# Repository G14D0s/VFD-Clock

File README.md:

# VFD-Clock
Mein Projekt für LF06: Das Wiedererwecken einer Fluoreszenz-Anzeige. 

# Ressourcen
Die Dokumentation / Ausarbeitung findet sich hier:
* [VFD - Ausarbeitung](Documentation/VFD-Ausarbeitung.md)
* [Videos](https://drive.google.com/drive/folders/1unJfzBfumFYsPnYGjSA5P8ESAhW6MluK?usp=sharing)
* [neuester Release mit PDF](https://github.com/G14D0s/VFD-Clock/releases/tag/Release)

***
# Diagramme
Mit [Obsidian](https://obsidian.md/) habe ich folgende Canvas-Dateien erstellt:
* [elektrischer Aufbau/Verbindungen](Documentation/VFD-Aufbau.png)
* [Konzept Programmierung](Documentation/VFD-Bildschirm_Programmierung.png)
* [Ablauf Multiplexing](Documentation/Ablauf_Multiplexing_VFD.png)

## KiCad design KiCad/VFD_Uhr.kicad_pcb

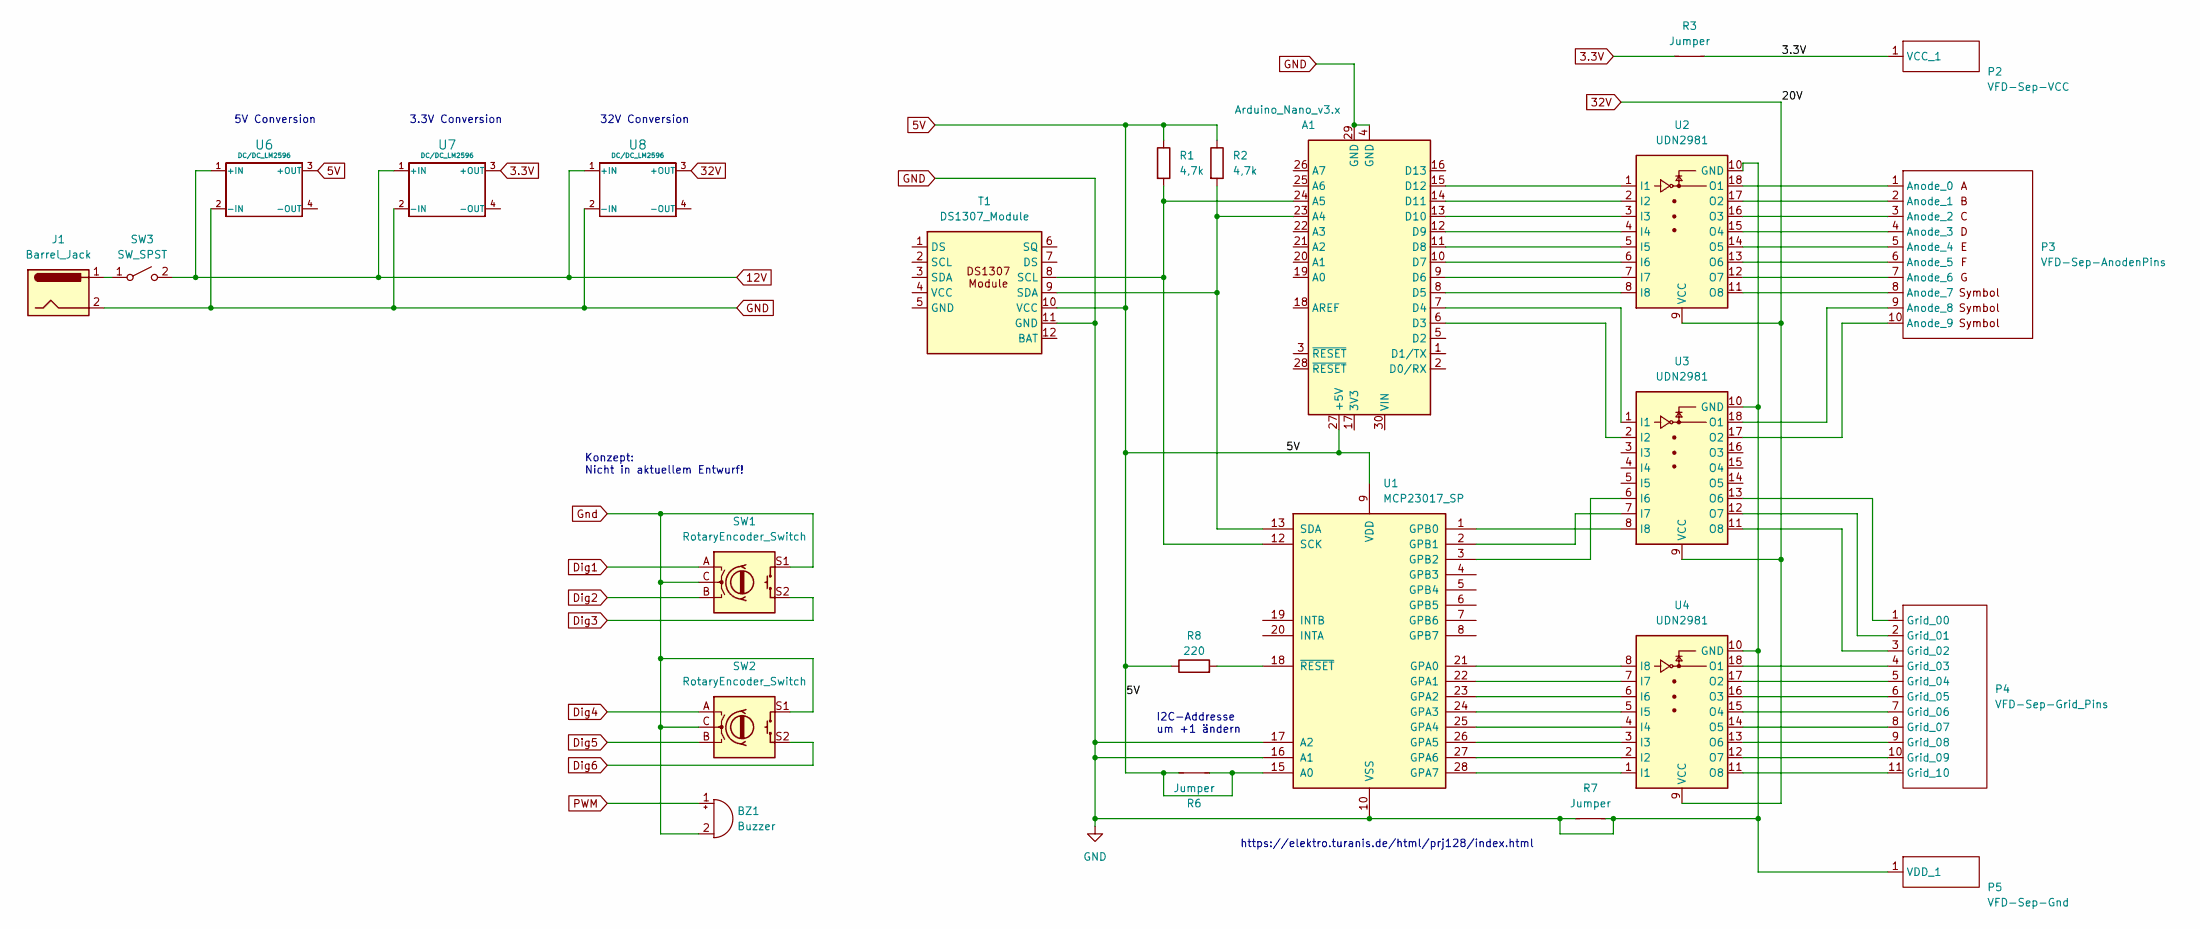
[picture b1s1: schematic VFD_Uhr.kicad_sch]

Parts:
A1: Arduino_Nano_v3.x; Arduino_Nano
BZ1: Buzzer; Buzzer_12x9.5RM7.6
J1: Barrel_Jack; BarrelJack_CUI_PJ-063AH_Horizontal_CircularHoles
P2: VFD-Sep-VCC; PinHeader_1x01_P2.54mm_Vertical
P3: VFD-Sep-AnodenPins; PinHeader_1x10_P2.54mm_Vertical
P4: VFD-Sep-Grid_Pins; PinHeader_1x11_P2.54mm_Vertical
P5: VFD-Sep-Gnd; PinHeader_1x01_P2.54mm_Vertical
R1, R2: 4,7k; R_Axial_DIN0207_L6.3mm_D2.5mm_P10.16mm_Horizontal
R3, R7: Jumper; 0-Resistor Jumper
R6: Jumper; Jumper-Wire_12mm_Red
R8: 220; R_Axial_DIN0207_L6.3mm_D2.5mm_P10.16mm_Horizontal
SW1, SW2: RotaryEncoder_Switch; RotaryEncoder_Alps_EC11E-Switch_Vertical_H20mm
SW3: SW_SPST; TerminalBlock_Phoenix_MPT-0,5-2-2.54_1x02_P2.54mm_Horizontal
T1: DS1307_Module
U1: MCP23017_SP; DIP-28_W7.62mm
U2, U3, U4: UDN2981; DIP-18_W7.62mm_Socket
U6, U7, U8: DC/DC_LM2596; DC_DC_LM2596_small

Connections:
3.3V: P2.1 (VCC_1), R3.1, R3.2, U7.3 (+OUT)
5V: A1.27 (+5V), R1.1, R2.1, R6.1, R6.2, R8.1, T1.10 (VCC), U1.9 (VDD), U1.15 (A0), U6.3 (+OUT)
12V: SW3.2 (B), U6.1 (+IN), U7.1 (+IN), U8.1 (+IN)
32V: U2.9 (VCC), U3.9 (VCC), U4.9 (VCC), U8.3 (+OUT)
Dig1: SW1.A
Dig2: SW1.B
Dig3: SW1.S2
Dig4: SW2.A
Dig5: SW2.B
Dig6: SW2.S2
GND: A1.4 (GND), A1.29 (GND), J1.2, P5.1 (VDD_1), R7.1, R7.2, T1.11 (GND), U1.10 (VSS), U1.16 (A1), U1.17 (A2), U2.10 (GND), U3.10 (GND), U4.10 (GND), U6.2 (-IN), U7.2 (-IN), U8.2 (-IN)
Gnd: BZ1.2 (+), SW1.C, SW1.S1, SW2.C, SW2.S1
unnamed: A1.23 (A4), R2.2, T1.9 (SDA), U1.13 (SDA)
unnamed: A1.24 (A5), R1.2, T1.8 (SCL), U1.12 (SCK)
unnamed: A1.6 (D3), U3.2 (I2)
unnamed: A1.7 (D4), U3.1 (I1)
unnamed: A1.8 (D5), U2.8 (I8)
unnamed: A1.9 (D6), U2.7 (I7)
unnamed: A1.10 (D7), U2.6 (I6)
unnamed: A1.11 (D8), U2.5 (I5)
unnamed: A1.12 (D9), U2.4 (I4)
unnamed: A1.13 (D10), U2.3 (I3)
unnamed: A1.14 (D11), U2.2 (I2)
unnamed: A1.15 (D12), U2.1 (I1)
unnamed: P3.1 (Anode_0), U2.18 (O1)
unnamed: P3.2 (Anode_1), U2.17 (O2)
unnamed: P3.3 (Anode_2), U2.16 (O3)
unnamed: P3.4 (Anode_3), U2.15 (O4)
unnamed: P3.5 (Anode_4), U2.14 (O5)
unnamed: P3.6 (Anode_5), U2.13 (O6)
unnamed: P3.7 (Anode_6), U2.12 (O7)
unnamed: P3.8 (Anode_7), U2.11 (O8)
unnamed: P3.9 (Anode_8), U3.18 (O1)
unnamed: P3.10 (Anode_9), U3.17 (O2)
unnamed: P4.1 (Grid_00), U3.13 (O6)
unnamed: P4.2 (Grid_01), U3.12 (O7)
unnamed: P4.3 (Grid_02), U3.11 (O8)
unnamed: P4.4 (Grid_03), U4.18 (O1)
unnamed: P4.5 (Grid_04), U4.17 (O2)
unnamed: P4.6 (Grid_05), U4.16 (O3)
unnamed: P4.7 (Grid_06), U4.15 (O4)
unnamed: P4.8 (Grid_07), U4.14 (O5)
unnamed: P4.9 (Grid_08), U4.13 (O6)
unnamed: P4.10 (Grid_09), U4.12 (O7)
unnamed: P4.11 (Grid_10), U4.11 (O8)
unnamed: J1.1, SW3.1 (A)
unnamed: U1.21 (GPA0), U4.8 (I8)
unnamed: U1.22 (GPA1), U4.7 (I7)
unnamed: U1.23 (GPA2), U4.6 (I6)
unnamed: U1.24 (GPA3), U4.5 (I5)
unnamed: U1.25 (GPA4), U4.4 (I4)
unnamed: U1.26 (GPA5), U4.3 (I3)
unnamed: U1.27 (GPA6), U4.2 (I2)
unnamed: U1.28 (GPA7), U4.1 (I1)
unnamed: U1.1 (GPB0), U3.8 (I8)
unnamed: U1.2 (GPB1), U3.7 (I7)
unnamed: U1.3 (GPB2), U3.6 (I6)
unnamed: R8.2, U1.18 (~RESET)
PWM: BZ1.1 (-)

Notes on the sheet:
5V Conversion
3.3V Conversion
https://elektro.turanis.de/html/prj128/index.html
32V Conversion
Konzept: Nicht in aktuellem Entwurf!
I2C-Addresse um +1 ändern

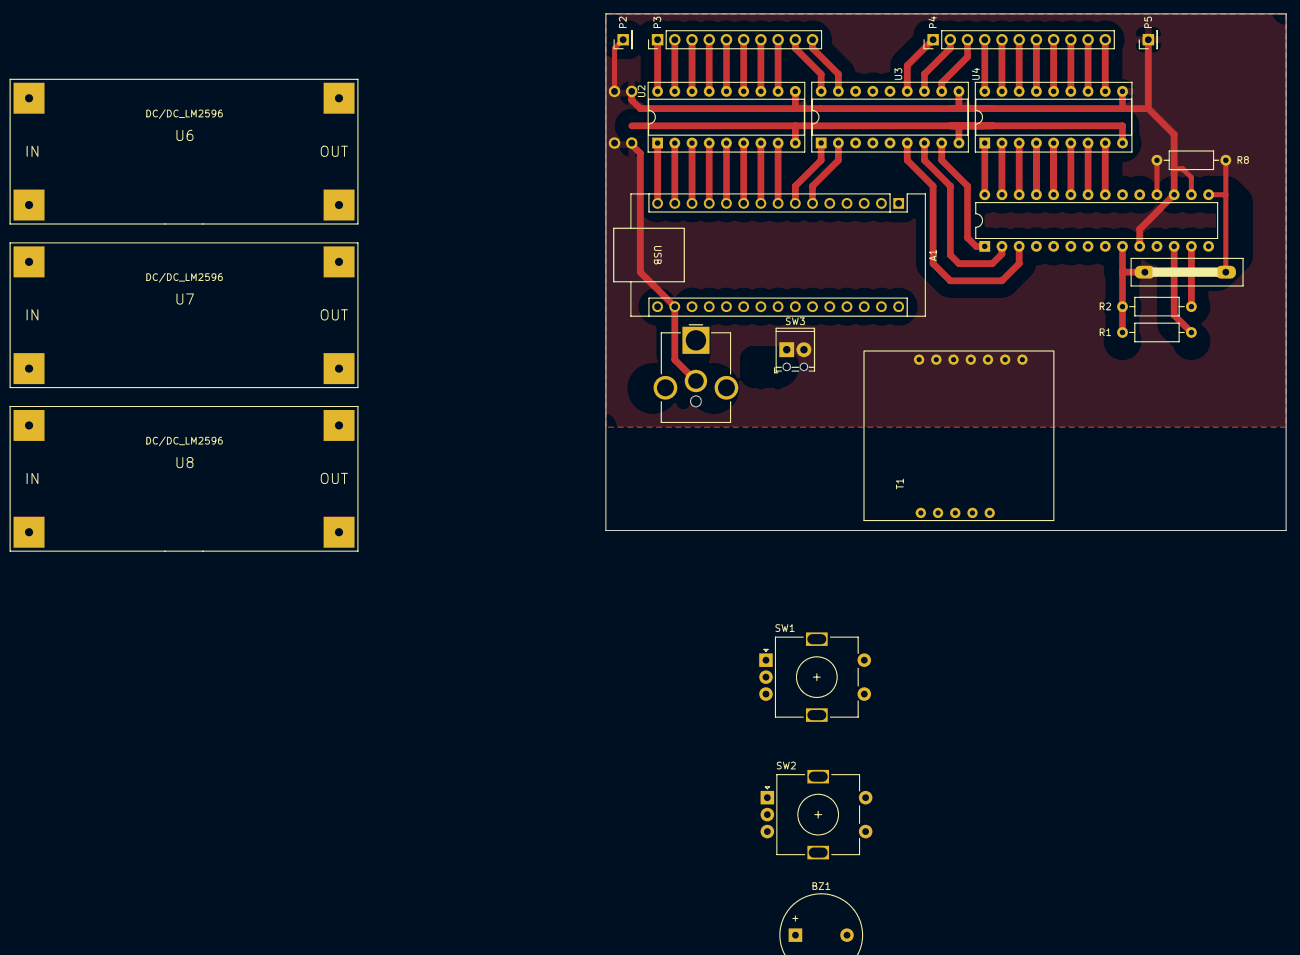
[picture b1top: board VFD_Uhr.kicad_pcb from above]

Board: 2 copper layers, 100.3 x 76.2 mm, 24 parts (0 on the bottom side), 52 nets.

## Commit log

2024-01-03 Initial Commit of all existing files
2024-01-04 Tested with DS3231
    As it turns out, the DS1307 library works with the DS3231 RTC Module just as well. So there's not a whole lot to change, although I have noticed a kind of bleeding between the segments
2024-01-15 Almost final changes
    I think that's it?
2024-01-15 Added KiCad Files
2024-01-15 Renaming and name attribution
2024-01-15 Exported Canvas from Obsidian
2024-01-15 Renamed File
